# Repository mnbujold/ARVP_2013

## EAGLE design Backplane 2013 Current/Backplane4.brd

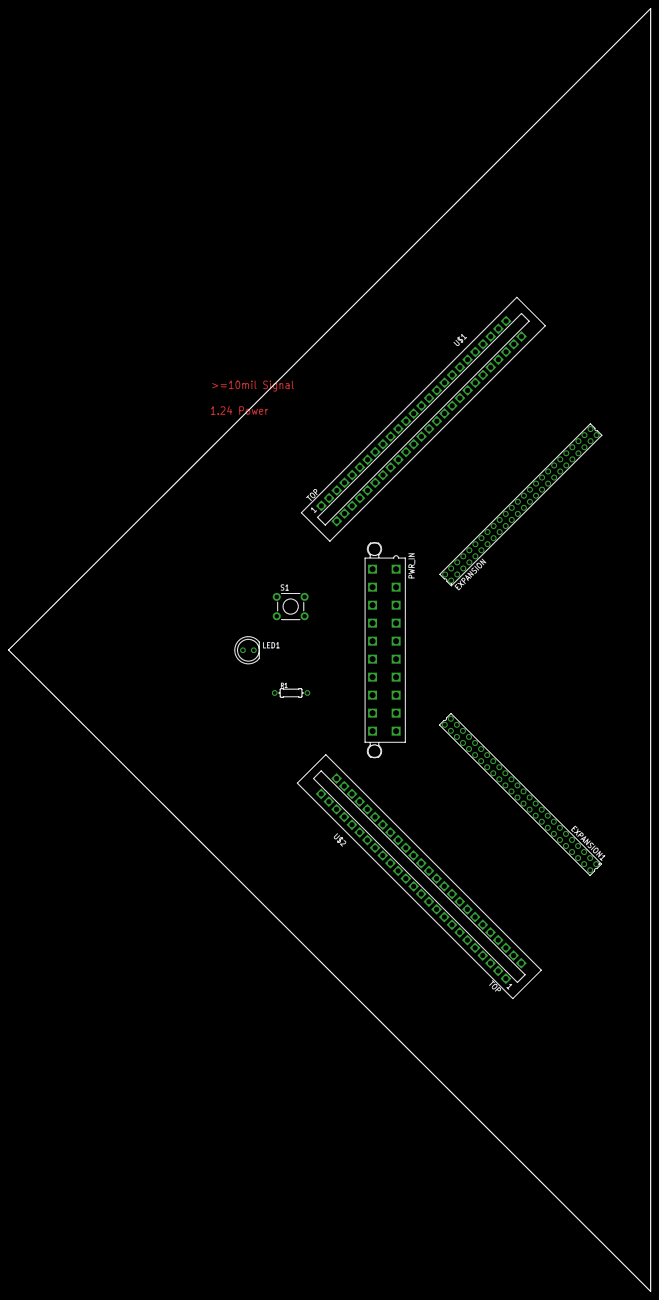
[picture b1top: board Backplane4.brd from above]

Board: 2 copper layers, 149.9 x 299.4 mm, 8 parts (0 on the bottom side), 52 nets, no tracks yet.

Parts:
EXPANSION, EXPANSION1: IDC_50PIN; 50PIN-IDC
LED1: LED5MM
PWR_IN: 5566-20
R1: 0204/7
S1: SWITCH-MOMENTARY-2PTH; TACTILE-PTH
U$1, U$2: CONN_50PIN

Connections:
3.3V: PWR_IN.1, PWR_IN.2, PWR_IN.11
3V3: EXPANSION.1, EXPANSION1.1, U$1.A1, U$2.A1
5V: EXPANSION.2, EXPANSION1.2, PWR_IN.4, PWR_IN.6, PWR_IN.19, PWR_IN.20, U$1.B1, U$2.B1
12V: EXPANSION.49, EXPANSION1.49, PWR_IN.10, U$1.A25, U$2.A25
DEPTH_SIG: EXPANSION.47, EXPANSION1.47, U$1.A24, U$2.A24
DIR_X0: EXPANSION.4, EXPANSION1.4, U$1.B2, U$2.B2
DIR_X1: EXPANSION.6, EXPANSION1.6, U$1.B3, U$2.B3
DIR_Y0: EXPANSION.8, EXPANSION1.8, U$1.B4, U$2.B4
DIR_Y1: EXPANSION.10, EXPANSION1.10, U$1.B5, U$2.B5
DIR_Z0: EXPANSION.12, EXPANSION1.12, U$1.B6, U$2.B6
DIR_Z1: EXPANSION.14, EXPANSION1.14, U$1.B7, U$2.B7
ETPU6: EXPANSION.15, EXPANSION1.15, U$1.A8, U$2.A8
ETPU7: EXPANSION.17, EXPANSION1.17, U$1.A9, U$2.A9
ETPU8: EXPANSION.19, EXPANSION1.19, U$1.A10, U$2.A10
ETPU9: EXPANSION.21, EXPANSION1.21, U$1.A11, U$2.A11
GND: EXPANSION.27, EXPANSION.28, EXPANSION.50, EXPANSION1.27, EXPANSION1.28, EXPANSION1.50, LED1.K, PWR_IN.3, PWR_IN.5, PWR_IN.7, PWR_IN.13, PWR_IN.15, PWR_IN.16, PWR_IN.17, S1.1, U$1.A14, U$1.B14, U$1.B25, U$2.A14, U$2.B14, U$2.B25
H_PHONE0: EXPANSION.43, EXPANSION1.43, U$1.A22, U$2.A22
H_PHONE1: EXPANSION.44, EXPANSION1.44, U$1.B22, U$2.B22
H_PHONE2: EXPANSION.45, EXPANSION1.45, U$1.A23, U$2.A23
H_PHONE3: EXPANSION.46, EXPANSION1.46, U$1.B23, U$2.B23
I2C_SCL: EXPANSION.25, EXPANSION1.25, U$1.A13, U$2.A13
I2C_SDA: EXPANSION.23, EXPANSION1.23, U$1.A12, U$2.A12
KILL_SIG: EXPANSION.48, EXPANSION1.48, U$1.B24, U$2.B24
MANI0: EXPANSION.35, EXPANSION1.35, U$1.A18, U$2.A18
MANI1: EXPANSION.36, EXPANSION1.36, U$1.B18, U$2.B18
MANI2: EXPANSION.37, EXPANSION1.37, U$1.A19, U$2.A19
MCP_CS: EXPANSION.20, EXPANSION1.20, U$1.B10, U$2.B10
MCP_STRB: EXPANSION.22, EXPANSION1.22, U$1.B11, U$2.B11
MCS_CS: EXPANSION.24, EXPANSION1.24, U$1.B12, U$2.B12
MCS_STRB: EXPANSION.26, EXPANSION1.26, U$1.B13, U$2.B13
unnamed: LED1.A, R1.1
unnamed: PWR_IN.14, S1.3
unnamed: PWR_IN.8, R1.2
PWM_X0: EXPANSION.3, EXPANSION1.3, U$1.A2, U$2.A2
PWM_X1: EXPANSION.5, EXPANSION1.5, U$1.A3, U$2.A3
PWM_Y0: EXPANSION.7, EXPANSION1.7, U$1.A4, U$2.A4
PWM_Y1: EXPANSION.9, EXPANSION1.9, U$1.A5, U$2.A5
PWM_Z0: EXPANSION.11, EXPANSION1.11, U$1.A6, U$2.A6
PWM_Z1: EXPANSION.13, EXPANSION1.13, U$1.A7, U$2.A7
SENSE0: EXPANSION.38, EXPANSION1.38, U$1.B19, U$2.B19
SPARE0: EXPANSION.16, EXPANSION1.16, U$1.B8, U$2.B8
SPARE1: EXPANSION.18, EXPANSION1.18, U$1.B9, U$2.B9
SPARE2: EXPANSION.39, EXPANSION1.39, U$1.A20, U$2.A20
SPARE3: EXPANSION.40, EXPANSION1.40, U$1.B20, U$2.B20
SPARE4: EXPANSION.41, EXPANSION1.41, U$1.A21, U$2.A21
SPARE5: EXPANSION.42, EXPANSION1.42, U$1.B21, U$2.B21
SPI_CLK: EXPANSION.33, EXPANSION1.33, U$1.A17, U$2.A17
SPI_CS1: EXPANSION.30, EXPANSION1.30, U$1.B15, U$2.B15
SPI_CS2: EXPANSION.32, EXPANSION1.32, U$1.B16, U$2.B16
SPI_CS3: EXPANSION.34, EXPANSION1.34, U$1.B17, U$2.B17
SPI_IN: EXPANSION.29, EXPANSION1.29, U$1.A15, U$2.A15
SPI_OUT: EXPANSION.31, EXPANSION1.31, U$1.A16, U$2.A16

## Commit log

2013-06-05 Thruster Controller Updated - Nearly Finalized
2013-06-06 Thruster ctl preliminary layout
2013-06-06 Thruster Ctl layout cont
2013-06-08 Minor updates
2013-06-15 Mainboard updates and interface card
2013-06-15 Interface card updates
2013-06-17 Thruster controller and mainboard updates
2013-06-17 Updated bus pin assignments
2013-06-18 thruster ctl updates
2013-06-19 thruster ctl update
2013-06-20 Thruster ctl error corrections, and more traces run
2013-06-25 More thruster ctl updates
2013-06-26 Thruster ctl and mainboard updates
2013-06-26 Thruster updates
2013-06-27 Thruster controller near completion
2013-06-27 Thruster ctl updates, just needs routing around ADC and RST circuit
2013-07-04 Mainboard updates, finalizing thruster ctl
2013-07-05 Mainboard updates
2013-07-08 Some minor updates
2013-07-10 More Mainboard updates
2013-07-11 Updated backplane dimensions
2013-07-12 More stuff done
2013-07-13 New attempt at mainboard-changed some pin assignments
2013-07-15 Before we try a crazy redesign...
2013-07-15 New revision of board - seems to work better...
2013-07-15 Moar mainboard updates
2013-07-16 Update mainboarde
2013-07-16 Other boards and updates
2013-07-16 Added pwr board
2013-07-17 Main board COMPLETE
2013-07-17 Tweaked CAM files - should work properly based on APC specs
2013-07-17 Thruster control done - add gnd plane and check board labelling
2013-07-17 Finalized updates
2013-09-03 Updated backplane
2014-02-18 Template for new board
2014-02-20 2014 updates
2014-02-26 board updates
